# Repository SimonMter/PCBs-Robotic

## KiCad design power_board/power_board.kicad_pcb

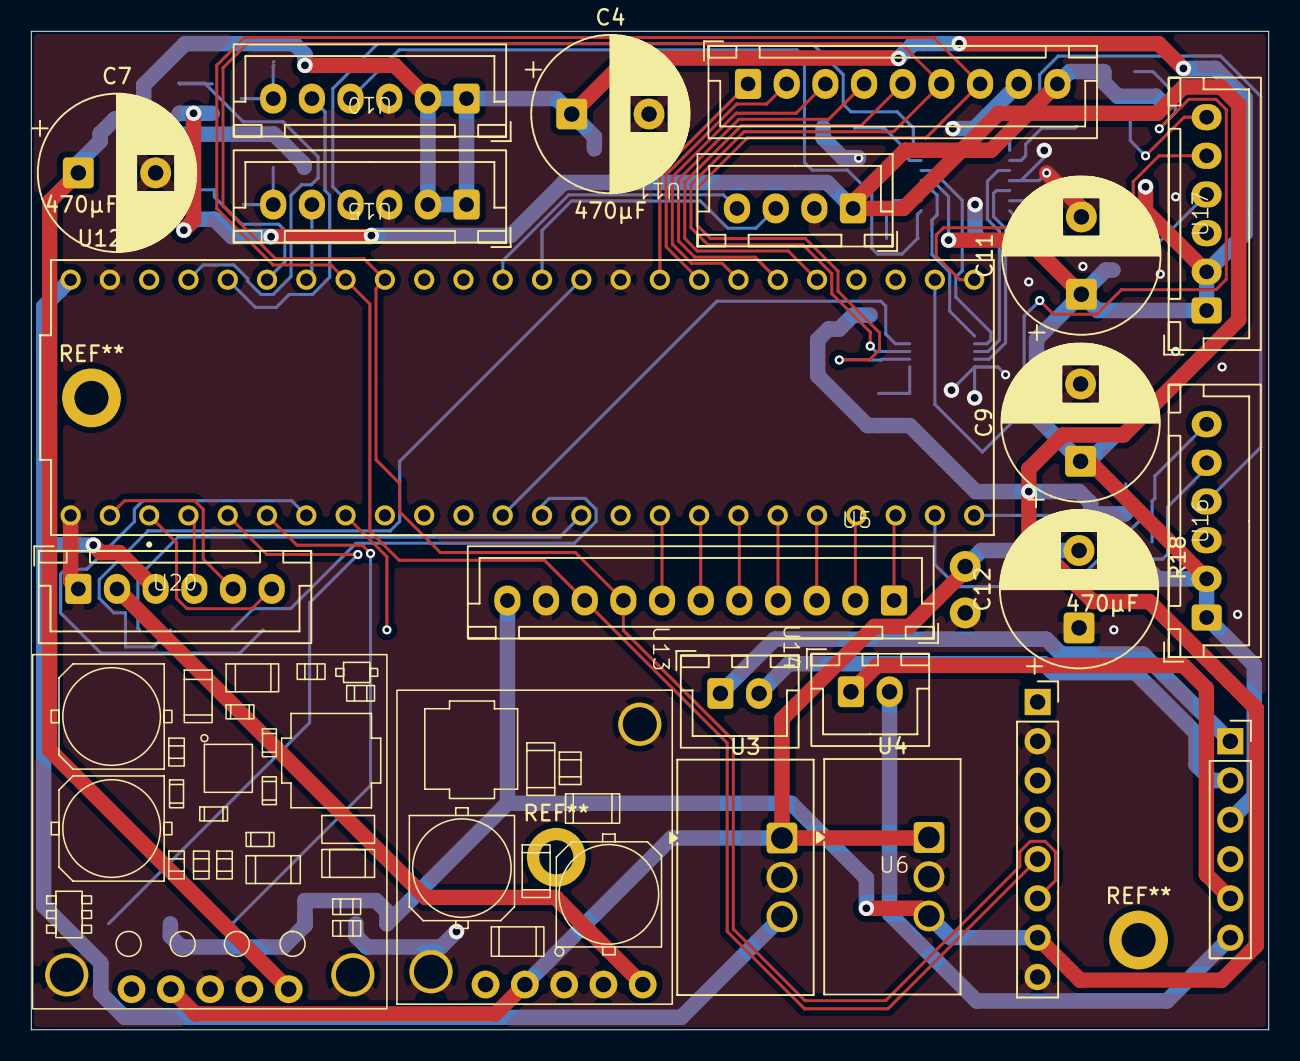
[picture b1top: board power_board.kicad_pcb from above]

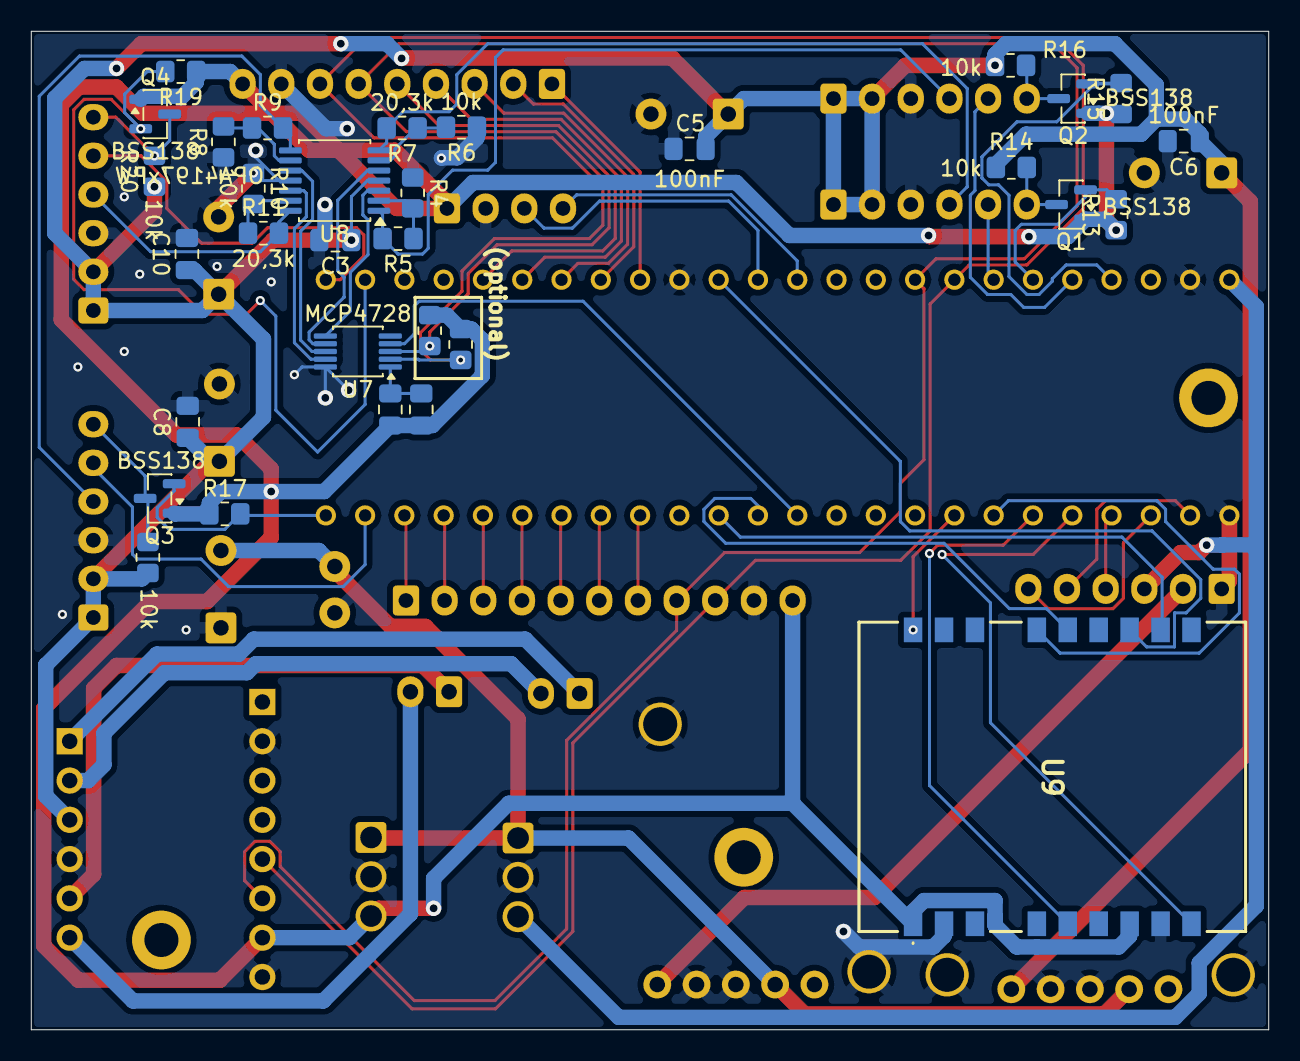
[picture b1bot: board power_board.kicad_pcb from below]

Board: 2 copper layers, 80.0 x 64.5 mm, 54 parts (32 on the bottom side), 62 nets.

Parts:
C1: 100nF ceramic; C_0805_2012Metric_Pad1.18x1.45mm_HandSolder
C2: 10microF; C_0805_2012Metric_Pad1.18x1.45mm_HandSolder
C3, C5, C6, C8, C10: 100nF; C_0805_2012Metric_Pad1.18x1.45mm_HandSolder
C4, C7, C9, C11, C12: 470µF; CP_Radial_D10.0mm_P5.00mm
Q1, Q2, Q3, Q4: BSS138; SOT-23
R1, R2: 4.7k; R_0805_2012Metric_Pad1.20x1.40mm_HandSolder
R4, R6, R8, R10, R13, R14, R15, R16, R17, R18, R19, R20: 10k; R_0805_2012Metric_Pad1.20x1.40mm_HandSolder
R5, R7, R9, R11: 20,3k; R_0805_2012Metric_Pad1.20x1.40mm_HandSolder
U1: S13V25F
U2: D24V
U3: TSR3-2450N; Converter_DCDC_TRACO_TSR2-24xxN_TSR2-24xxxN_THT
U4: TSR3-2433N; Converter_DCDC_TRACO_TSR2-24xxN_TSR2-24xxxN_THT
U5: LipoPins
U6: Motron M2T256
U7: MCP4728; MSOP-10_3x3mm_P0.5mm
U8: OPA4197xPW; TSSOP-14_4.4x5mm_P0.65mm
U9: FSM300
U10, U15, U16, U17: motor_faulhaber
U11: QTRXL-HD-01A
U12: Teensy4.1OuterPins; Teensy4-1OuterPins
U13, U14: Motor DropOff
U18: back_board_connector
U19: connector front tof
U20: Pi Connector

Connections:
+3.3V: C1.1, C2.1, Q1.1 (G), Q2.1 (G), Q3.1 (G), Q4.1 (G), R1.1, R2.1, R13.1, R15.1, R17.1, R19.1, U4.3 (Vout), U6.7 (VDD), U9.1 (VDD), U9.7 (PS1), U11.1 (VCC), U18.9 (3.3V), U19.10 (3.3V)
+5V: U3.3 (Vout), U12.VIN, U20.3 (5V)
+12V: C3.1, C4.1, C5.1, C6.1, C7.1, C8.1, C9.1, C10.1, C11.1, R14.1, R16.1, R18.1, R20.1, U1.OUT (VOUT), U6.11 (VIN), U8.4 (V+), U10.1 (U_P), U10.2 (U_MOT), U15.1 (U_P), U15.2 (U_MOT), U16.1 (U_P), U16.2 (U_MOT), U17.1 (U_P), U17.2 (U_MOT)
/5V PI: U2.OUT (VOUT), U20.2 (5V_PI)
/12V Lipo: C12.2, U1.VIN, U2.VIN, U3.1 (Vin), U4.1 (Vin), U5.1 (12V_Lipo)
/DIR1: U10.5 (DIR), U12.22 (A8)
/DIR2: U12.20 (A6), U15.5 (DIR)
/DIR3: U12.31 (CTX3), U16.5 (DIR)
/DIR4: U12.33 (MCLK2), U17.5 (DIR)
/FG_M1: Q2.3 (D), R16.2, U10.6 (FG)
/FG_M2: Q1.3 (D), R14.2, U15.6 (FG)
/FG_M3: Q3.3 (D), R18.2, U16.6 (FG)
/FG_M4: Q4.3 (D), R20.2, U17.6 (FG)
/FG_T1: Q2.2 (S), R15.2, U12.23 (A9)
/FG_T2: Q1.2 (S), R13.2, U12.21 (A7)
/FG_T3: Q3.2 (S), R17.2, U12.32 (OUT1B)
/FG_T4: Q4.2 (S), R19.2, U12.34 (RX8)
/G-CSN: U9.15 (CSN), U12.5 (IN2)
/G-HINTN: U9.5 (HINTN), U12.4 (BCLK2)
/G-NRST: U9.18 (NRST), U12.6 (OUT1D)
/LDAC: U7.4 (~LDAC), U12.10 (CS1)
/LED_CP: U12.2 (OUT2), U20.4 (WS_DATA)
/M1A: U6.9 (M1A), U13.1 (VIN)
/M1B: U6.10 (M1B), U13.2 (GND)
/M2A: U6.13 (M2A), U14.1 (VIN)
/M2B: U6.14 (M2B), U14.2 (GND)
/MCLK: U9.12 (SCK), U12.13 (SCK)
/MISO: U9.11 (MISO), U12.12 (MISO)
/MOSI: U9.14 (MOSI), U12.11 (MOSI)
/MOT_A_SHIFTED: R5.2, U8.1, U10.4 (U_NSOL)
/MOT_A_UNSHIFTED: U7.6 (VOUTA), U8.3 (+)
/MOT_B_SHIFTED: R7.2, U8.7, U15.4 (U_NSOL)
/MOT_B_UNSHIFTED: U7.7 (VOUTB), U8.5 (+)
/MOT_C_SHIFTED: R9.2, U8.8, U16.4 (U_NSOL)
/MOT_C_UNSHIFTED: U7.8 (VOUTC), U8.10 (+)
/MOT_D_SHIFTED: R11.2, U8.14, U17.4 (U_NSOL)
/MOT_D_UNSHIFTED: U7.9 (VOUTD), U8.12 (+)
/RX2PI: U12.0 (RX1), U20.5 (RX)
/SCL: R1.2, U6.5 (SCL), U7.2 (SCL), U12.19 (A5), U18.7 (SCL), U19.8 (SCL)
/SDA: R2.2, U6.6 (SDA), U7.3 (SDA), U12.18 (A4), U18.6 (SDA), U19.7 (SDA)
/S_CTRL: U11.3 (CTRL), U12.14 (A0)
/S_S: U11.4 (S), U12.15 (A1)
/TASTER_L: U12.25 (A11), U19.5 (Taster_L)
/TASTER_R: U12.24 (A10), U19.6 (Taster_R)
/TX2PI: U12.1 (TX1), U20.6 (TX)
/WAKEN: U9.9 (PS0/WAKEN), U12.3 (LRCLK2)
/XSHUT1: U12.30 (CRX3), U19.0 (XShut_1)
/XSHUT2: U12.29 (TX7), U19.1 (XShut_2)
/XSHUT3: U12.28 (RX7), U19.2 (XShut_3)
/XSHUT4: U12.27 (A13), U19.3 (XShut_4)
/XSHUT5: U12.26 (A12), U19.4 (XShut_5)
/XSHUT6: U12.41 (A17), U18.1 (X_SHUT1)
/XSHUT7: U12.40 (A16), U18.2 (X_SHUT2)
/XSHUT8: U12.39 (A15), U18.3 (X_SHUT3)
/XSHUT9: U12.38 (A14), U18.4 (X_SHUT4)
/XSHUT10: U12.37 (CS3), U18.5 (X_SHUT5)
GND: C3.2, C4.2, C5.2, C6.2, C7.2, C8.2, C9.2, C10.2, C11.2, C12.1, R4.1, R6.1, R8.1, R10.1, U1.GND, U2.GND, U3.2 (GND), U4.2 (GND), U5.2 (GND), U6.2 (GND), U6.8 (GND), U6.12 (GND), U7.10 (VSS), U8.11 (V-), U9.2 (GND), U9.8 (GND), U10.3 (GND), U11.2 (GND), U12.GND1 (GND), U12.GND2 (GND__1), U12.GND3 (GND__2), U15.3 (GND), U16.3 (GND), U17.3 (GND), U18.8 (GND), U19.9 (GND), U20.1 (GND)
unnamed: C1.2, C2.2, U7.1 (VDD)
unnamed: R4.2, R5.1, U8.2 (-)
unnamed: R6.2, R7.1, U8.6 (-)
unnamed: R8.2, R9.1, U8.9 (-)
unnamed: R10.2, R11.1, U8.13 (-)

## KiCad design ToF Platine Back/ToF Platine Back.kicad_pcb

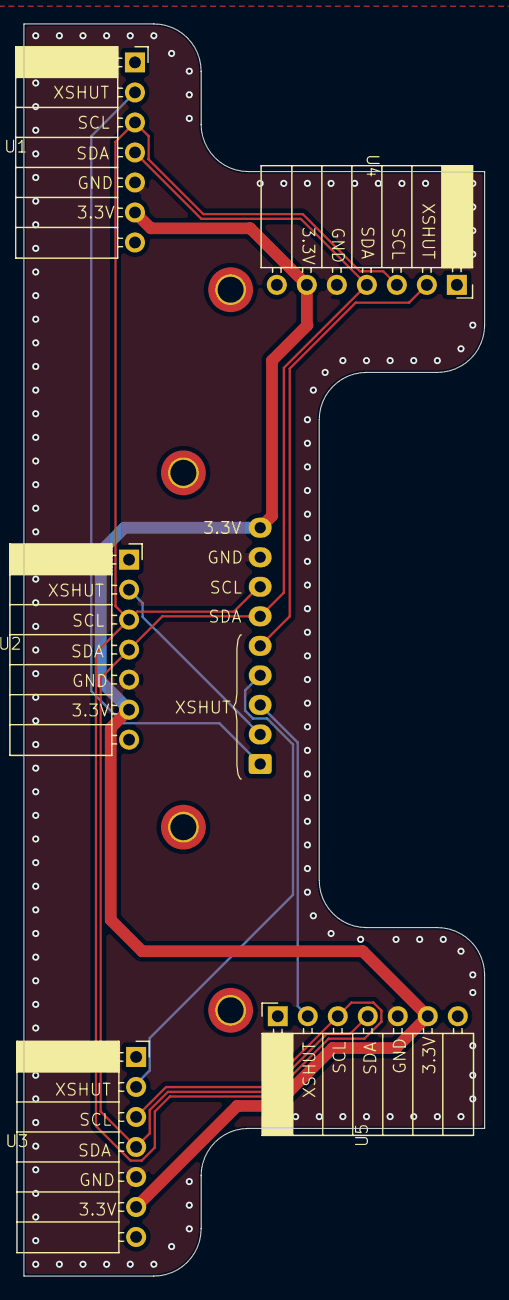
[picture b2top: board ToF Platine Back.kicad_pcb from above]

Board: 2 copper layers, 39.0 x 106.0 mm, 6 parts (1 on the bottom side), 9 nets.

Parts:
U1, U2, U3, U4, U5: VL53L1X
U6: back_board_connector

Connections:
+3.3V: U1.2 (VIN), U2.2 (VIN), U3.2 (VIN), U4.2 (VIN), U5.2 (VIN), U6.9 (3.3V)
/SCL: U1.5 (SCL), U2.5 (SCL), U3.5 (SCL), U4.5 (SCL), U5.5 (SCL), U6.7 (SCL)
/SDA: U1.4 (SDA), U2.4 (SDA), U3.4 (SDA), U4.4 (SDA), U5.4 (SDA), U6.6 (SDA)
/X_SHUT1: U1.6 (XSHUT), U6.1 (X_SHUT1)
/X_SHUT2: U2.6 (XSHUT), U6.2 (X_SHUT2)
/X_SHUT3: U5.6 (XSHUT), U6.3 (X_SHUT3)
/X_SHUT4: U3.6 (XSHUT), U6.4 (X_SHUT4)
/X_SHUT5: U4.6 (XSHUT), U6.5 (X_SHUT5)
GND: U1.3 (GND), U2.3 (GND), U3.3 (GND), U4.3 (GND), U5.3 (GND), U6.8 (GND)

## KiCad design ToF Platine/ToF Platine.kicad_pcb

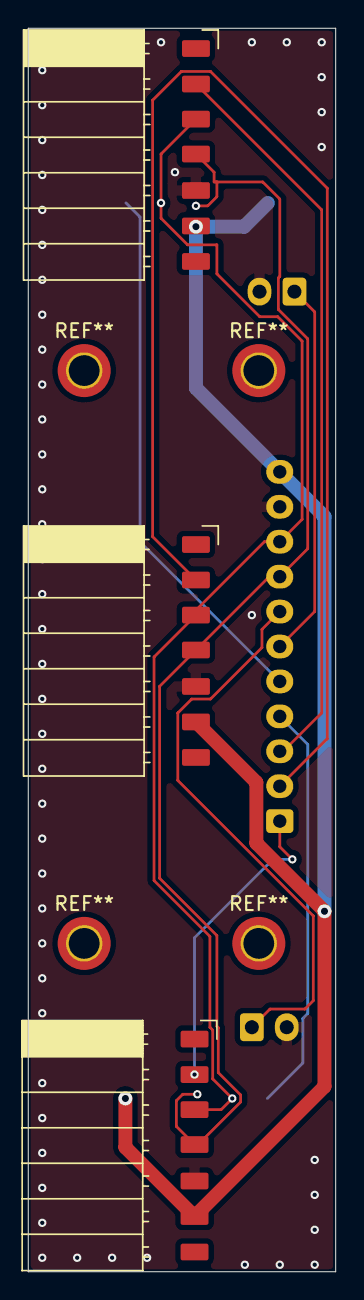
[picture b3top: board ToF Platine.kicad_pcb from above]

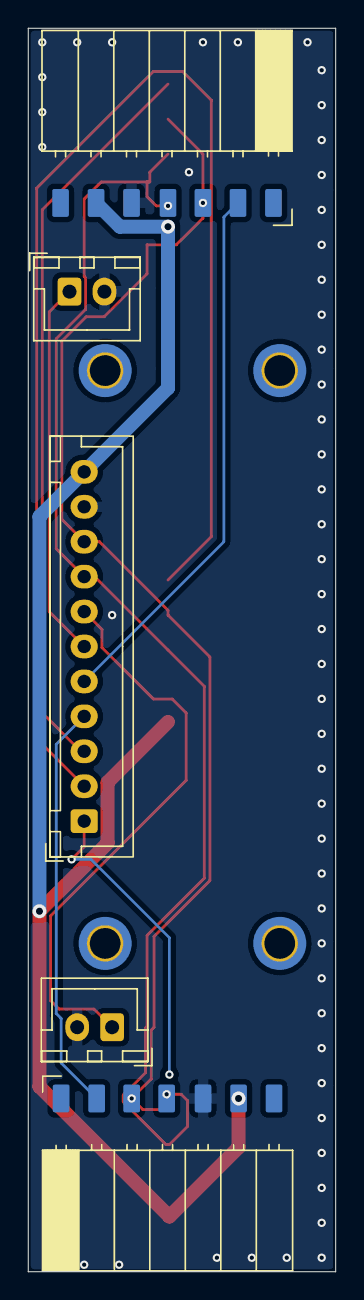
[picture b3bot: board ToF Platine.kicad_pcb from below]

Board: 2 copper layers, 22.0 x 89.0 mm, 8 parts (5 on the bottom side), 11 nets.

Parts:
U1, U3, U4, U5, U8: VL53L1X SMD
U2: front_board_connector
U6, U7: Taster

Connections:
+3.3V: U1.2 (VIN), U2.10 (3.3V), U3.2 (VIN), U4.2 (VIN), U5.2 (VIN), U8.2 (VIN)
/GPIO_Taster_L: U2.5 (Taster_L), U6.1 (GPIO)
/GPIO_Taster_R: U2.6 (Taster_R), U7.1 (GPIO)
/SCL: U1.5 (SCL), U2.8 (SCL), U3.5 (SCL), U4.5 (SCL), U5.5 (SCL), U8.5 (SCL)
/SDA: U1.4 (SDA), U2.7 (SDA), U3.4 (SDA), U4.4 (SDA), U5.4 (SDA), U8.4 (SDA)
/XShut_1: U1.6 (XSHUT), U2.0 (XShut_1)
/XShut_2: U2.1 (XShut_2), U3.6 (XSHUT)
/XShut_3: U2.2 (XShut_3), U4.6 (XSHUT)
/XShut_4: U2.3 (XShut_4), U5.6 (XSHUT)
/XShut_5: U2.4 (XShut_5), U8.6 (XSHUT)
GND: U1.3 (GND), U2.9 (GND), U3.3 (GND), U4.3 (GND), U5.3 (GND), U6.2 (GND), U7.2 (GND), U8.3 (GND)
